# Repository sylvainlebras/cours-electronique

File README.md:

# cours-electronique
 Application pratiques d'électronique

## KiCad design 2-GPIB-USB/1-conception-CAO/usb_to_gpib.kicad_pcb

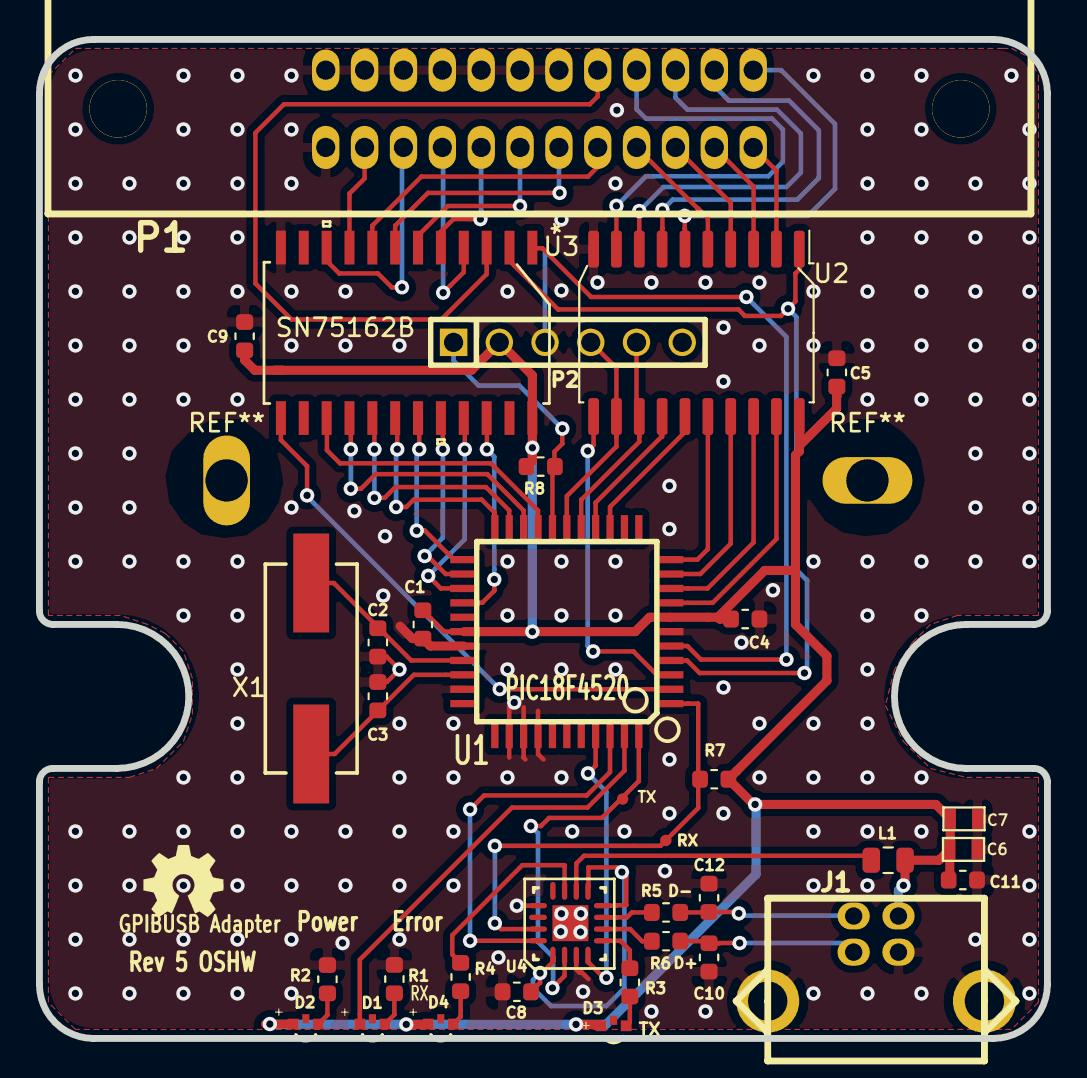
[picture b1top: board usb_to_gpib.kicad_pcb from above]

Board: 2 copper layers, 56.0 x 55.5 mm, 35 parts (0 on the bottom side), 58 nets.

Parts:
1PIN: P4; 1pin
1PIN#2: P3; 1pin
C1, C4, C5, C9: 100nF; C_0603_1608Metric
C2, C3: 18pF; C_0603_1608Metric
C6: 4.7uF; SM0603
C7: 100nF; SM0603
C8, C11: 10nF; C_0603_1608Metric
C10, C12: 47pF; C_0603_1608Metric
D1, D2, D3, D4: LED; WL-SMSW_0603_ROUND
J1: Conn1; conn_usb_B
L1: INDUCTOR; L_0805_2012Metric
P1: CONN_12X2; gpib_conn_male
P2: CONN_6; PIN_ARRAY-6X1
R1, R3: 1k; R_0603_1608Metric
R2, R4: 4k7; R_0603_1608Metric
R5, R6: 270; R_0603_1608Metric
R7: 22k; R_0603_1608Metric
R8: 10k; R_0603_1608Metric
U1: PIC18F4520; TQFP44
U2: SN75160B; SOIC-20W_7.5x12.8mm_P1.27mm
U3: SN75162B; SN75162BDW
U4: FT230X; QFN24
X1: CRYSTAL; 4HSMX

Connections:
3V3OUT: C8.1, U4.1, U4.8, U4.9
ATN: U1.20, U3.16
DAV: U1.22, U3.18
DC: U1.2, U3.13
DGND: C1.2, C2.2, C3.1, C4.1, C5.2, C6.2, C7.2, C8.2, C9.2, C10.2, C11.2, C12.2, J1.4, J1.5, J1.6, P1.12, P1.18, P1.19, P1.20, P1.21, P1.22, P1.23, P1.24, P2.3, R1.1, R2.1, U1.6, U1.29, U1.32, U1.35, U1.36, U1.37, U2.10, U3.12, U4.3, U4.13
DIO1: U1.8, U2.19
DIO2: U1.9, U2.18
DIO3: U1.10, U2.17
DIO4: U1.11, U2.16
DIO5: U1.14, U2.15
DIO6: U1.15, U2.14
DIO7: P2.5, U1.16, U2.13
DIO8: P2.4, U1.17, U2.12
EOI: U1.21, U3.17
ERROR_LED: D1.2, U1.43
FTDI_CTS: U1.41, U4.4
FTDI_RTS: U1.42, U4.16
FTDI_RXI: 1PIN#2.1, U1.44, U4.2
FTDI_TXO: 1PIN.1, R7.1, U1.1, U4.15
G_ATN: P1.11, U3.9
G_DAV: P1.6, U3.7
G_DIO1: P1.1, U2.2
G_DIO2: P1.2, U2.3
G_DIO3: P1.3, U2.4
G_DIO4: P1.4, U2.5
G_DIO5: P1.13, U2.6
G_DIO6: P1.14, U2.7
G_DIO7: P1.15, U2.8
G_DIO8: P1.16, U2.9
G_EOI: P1.5, U3.8
G_IFC: P1.9, U3.4
G_NDAC: P1.8, U3.5
G_NRFD: P1.7, U3.6
G_REN: P1.17, U3.3
G_SRQ: P1.10, U3.10
IFC: U1.25, U3.21
NDAC: U1.24, U3.20
NRFD: U1.23, U3.19
unnamed: C2.1, U1.30, X1.1
unnamed: C3.2, U1.31, X1.2
unnamed: C10.1, J1.3, R6.1
unnamed: C12.1, J1.2, R5.1
unnamed: D1.1, R1.2
unnamed: D2.1, R2.2
unnamed: D3.1, R3.2
unnamed: D4.1, R4.2
unnamed: L1.1, U4.10
unnamed: P2.1, R8.1, U1.18
PE: U1.3, U2.11
REN: U1.26, U3.22
RX_LED: R4.1, U4.11
SC: U1.5, U3.1
SRQ: U1.19, U3.15
TE: U1.4, U2.1, U3.2
TX_LED: R3.1, U4.5
USB_D+: R6.2, U4.6
USB_D-: R5.2, U4.7
VCC: C1.1, C4.2, C5.1, C6.1, C7.1, C9.1, C11.1, D2.2, D3.2, D4.2, J1.1, L1.2, P2.2, R7.2, R8.2, U1.7, U1.28, U2.20, U3.24

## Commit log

2020-12-04 Création
    Mise a jour
2020-12-04 Correction perçages GPIB-USB
    Percage oblongs non métalisés

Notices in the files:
2-GPIB-USB/1-conception-CAO/usb_to_gpib.kicad_pcb:
Released under Creative Commons
Attribution-ShareAlike 3.0 License
parts and their libraries:
Copyright 2016 Accelerated Designs. All rights reserved.
